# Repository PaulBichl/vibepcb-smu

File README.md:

# VibePCB SMU

A 1-channel, 4-quadrant source/measure unit (bipolar lab supply that also sinks):
**+-30 V, +-1 A**, powered from a **USB-C PD charger (20 V)**, controlled over **Ethernet**,
voltage and current on two 4-digit 7-segment displays. Designed with
[VibePCB](https://github.com/PaulBichl/vibepcb) (tscircuit -> KiCad).

| Board | Layers | Size | Content |
|-------|--------|------|---------|
| `boards/smu-main` | 4 (top+GND / GND / route+GND / bottom+GND) | 160 x 100 mm | USB-C PD input, rail converters, OPA548 output stage, control loop, 24-bit measurement, STM32G431 + W5500 |
| `boards/smu-front` | 2 (both GND-poured) | 150 x 45 mm | 2x SR420561N displays, TM1640 driver, 6 status LEDs, OUTPUT / MODE buttons |

The boards are joined by a 10-way ribbon (main J5 <-> front J1). The output terminal (main J3:
HI, S+, S-, LO) is wired to front-panel binding posts; the OPA548 (TO-220-7) bolts to a heatsink
on the rear panel (with a fan on J4).

## Look at it

| | Main board | Display board |
|---|---|---|
| Schematic | [PDF](boards/smu-main/hardware/smu-main-schematic.pdf) | [PDF](boards/smu-front/hardware/smu-front-schematic.pdf) |
| Layout | [PDF, one page per copper layer](boards/smu-main/hardware/smu-main-layout.pdf), [front](boards/smu-main/hardware/smu-main-layout-front.png), [back](boards/smu-main/hardware/smu-main-layout-back.png) | [PDF](boards/smu-front/hardware/smu-front-layout.pdf), [front](boards/smu-front/hardware/smu-front-layout-front.png), [back](boards/smu-front/hardware/smu-front-layout-back.png) |
| 3D | [top](boards/smu-main/hardware/smu-main-top.png), [bottom](boards/smu-main/hardware/smu-main-bottom.png) | [top](boards/smu-front/hardware/smu-front-top.png), [bottom](boards/smu-front/hardware/smu-front-bottom.png) |
| BOM (LCSC / MPN) | [CSV](boards/smu-main/hardware/smu-main-bom.csv) | [CSV](boards/smu-front/hardware/smu-front-bom.csv) |
| KiCad project | [kicad/](boards/smu-main/hardware/kicad) | [kicad/](boards/smu-front/hardware/kicad) |

Both boards pass KiCad's DRC and ERC with 0 errors. The KiCad projects open as they are (3D
models left out: they are tens of MB; `pcb fix` downloads them). Gerbers / pick-and-place are
not in the repo: open the project in KiCad and plot them, or build the boards (below) and run
`hatch run pcb fab <board>` for Gerbers, drill, BOM, CPL and a JLCPCB upload set.

## Setup / build

Same as the [CO2 example](https://github.com/PaulBichl/vibepcb-example-co2-monitor): clone
`vibepcb` next to this repo as `VibePCB`, then

```bash
hatch run setup
hatch run pcb all smu-main
hatch run pcb all smu-front
cd boards/smu-main/sim && ./run_cases.sh && ./verify.sh   # loop simulations (ngspice)
```

## Architecture

```
USB-C PD (STUSB4500, 20 V) -> P-FET -> VIN -+-> 5 V buck -> 3.3 V (digital), 3.3 V (analog), -4.35 V (charge pump)
                                            +-> SEPIC (LM5156)            V+ = +4.5 .. +34 V  (PWM-tracked)
                                            +-> inverting (LMR51635)      V- = -5 .. -34 V    (PWM-tracked)
DAC8563 (VSET, ISET) -> summing node -> OPA548 -> relay -> HI ... DUT ... LO -> 0.1 R shunt -> GND
                          ^  ^  current-limit integrators (OPA2192) <- INA828 (-1 V/A)
                          |  +-- S+ (remote sense, 100 R to HI inside)
ADS131M02: V = (S+ - S-)/31, I = INA828 output    STM32G431 <-> W5500 <-> RJ45, TM1640 front panel
```

### Output stage

- OPA548 as inverting summing amplifier with remote sense:
  `V(S+) - V(S-) = 30 V - 24 * VSET` (VSET = DAC A, 0..2.5 V, 16 bit -> ~0.9 mV steps).
  The + input sees S- through the matching divider (120k / 3x 10k), so the shunt drop and the
  LO lead resistance are cancelled. S+/S- fall back to HI/LO through 100 R when no sense leads
  are connected (and to the amplifier output through 4.7k while the relay is open).
- Current limit +-ISET/2 A (ISET = DAC B): two integrators compare the INA828 output (-1 V/A)
  with +-ISET and pull the summing node through diodes. PI zero (12k * 47n) sits on the power
  stage pole (120k * 4.7n). Simulated: stable from a dead short to open circuit, with 10-100 uF
  loads, all four quadrants (`sim/`).
- Fast protection: the OPA548's own current limit, fixed at ~1.1 A by R109 (49.9k ILIM to V-,
  I = 15000 * 4.75 V / (13.75k + R)). It catches load steps in microseconds; the precise analog
  limit takes over within ~2-7 ms.
- Output relay (HFD4/5, both poles in parallel), output TVS (SMBJ36CA), clamp diodes from the
  amplifier output to both rails, 1 uF across the terminals. R118 (0.47 Ohm) between amplifier and
  relay keeps the OPA548 stable into capacitive loads (see Performance estimates).

### Tracking rails

The OPA548 only gets the headroom it needs, which keeps its dissipation low and the supply
span within its 60 V rating:

- Firmware: `V+ = max(Vout_max + 4 V, 4.5 V)`, `V- = min(Vout_min - 4 V, -5 V)` where
  Vout_max/min cover the setpoint and the measured output. Sourcing 1 A at 0 V dissipates ~4.5 W
  instead of ~34 W with fixed rails. Sinking is limited by physics (P = Vout * I goes into the
  heatsink): plan for a firmware power limit (e.g. 25 W, more with the fan).
- Hardware span clamp: a 51 V zener + 1k from V+ into the V- feedback node reduces |V-| when
  V+ - V- would exceed ~52 V, whatever the firmware does.
- At reset (MCU pins high-Z): both rails at minimum (pull-up / pull-down on the PWM pins),
  OPA548 hardware current limit 0 A, OPA548 disabled (opto LED on), relay open.

### Measurement

ADS131M02 (24 bit, simultaneous sampling, internal 1.2 V reference, 8.192 MHz oscillator):
- CH0: `(S+ - S-) / 31` through 0.1 % 300k/10k dividers -> +-36 V full scale.
- CH1: INA828 output, -1 V/A -> +-1.2 A full scale.

Firmware calibrates offset/gain of VSET, ISET and both ADC channels against a DMM (store in
flash) and can close a slow digital loop on top of the analog one.

## Performance estimates (simulated)

`boards/smu-main/sim/perf.sh` runs the loop with TI's vendor models (OPA548, INA828, OPA2192;
`fetch_models.sh` downloads them, they are not committed) in ngspice, rails tracking as the
firmware sets them. DAC8563 noise from its datasheet (90 nV/rtHz DAC + 250 nV/rtHz internal
reference, which also feeds REFN, so it cancels at 0 V out). Not simulated: switcher ripple /
PSRR, drift, INL, layout parasitics.

| Quantity | Estimate |
|----------|----------|
| Setting resolution | V: 0.92 mV (16 bit over 60 V), I limit: 19 uA (16 bit over 1.25 A) |
| Uncalibrated error (nominal parts) | V: +90 mV offset (OPA548 Vos/Ib x noise gain 37); I: +0.7 % gain (INA828 G = 9.93) - both removed by the 2-point calibration; 0.1 % resistors add ~0.15 % gain |
| Measurement noise (ADS131M02, 1 kSPS) | V: ~0.1 mVrms (3 uVrms x 31 divider); I: ~4 uArms (ADC + INA828) |
| Four quadrants | +-10 V / +-1 A source and +-11.5 V / 0.5 A sink cases regulate as set |
| Setpoint bandwidth | 270 Hz (-3 dB); 10-90 % rise 1.24 ms; within 10 mV of a 10 V step after ~4 ms; no overshoot with 1 / 10 / 100 uF loads |
| CV loop | phase margin 53 deg (1 uF on board only), 79 deg (+10 uF), 81 deg (+100 uF); crossover ~450 kHz |
| Output impedance (CV) | 23 mOhm at 10 Hz, 0.2 Ohm at 100 Hz, 0.59 Ohm at 1-10 kHz |
| Load step 0.5 -> 1 A at 10 V | dips 0.29 V, back within 10 mV after 0.63 ms |
| Short at 1 A limit | peak 1.20 A (OPA548 limit), within 1 % of 1 A after 6.6 ms; short removed: no overshoot |
| Output noise (10 Hz-100 kHz) | 97 uVrms at 0 V, 115 uVrms at 30 V; 1.15 uV/rtHz at 1 kHz |
| OPA548 dissipation at 1 A | source: 4-4.5 W (tracking rails); sink: (Vout + 5 V) x I, 35 W at +30 V |
| Heatsink (Tj <= 125 C, Ta 35 C) | 4.5 W: <= 18 K/W (passive); 25 W firmware limit: <= 1.7 K/W (fan); sink at 30 V / 0.71 A max under 25 W |
| USB-C PD input | worst case (source 30 V / 1 A) ~43 W -> ~2.2 A at 20 V: a 60 W (3 A) PD supply |

Found by the vendor models: the OPA548 oscillates into the 1 uF output capacitor (0.73 Vpp at
10 V out, `dc0_without_r118`); the behavioural model (`loop.cir`, single pole) hid it. R118
(0.47 Ohm, 2 W) between the amplifier and the relay isolates it; C104 keeps the fast feedback
on the amplifier side, the remote sense removes its DC drop.

## MCU pin map (STM32G431RBT6, LQFP-64)

No radio: control is over Ethernet only. Flashing: USB DFU over the USB-C (hold BOOT0 = SW2,
press RESET = SW1) or SWD on J6 (3V3, SWDIO, SWCLK, NRST, GND). 8 MHz crystal (Y2) on PF0/PF1.

| Pin | Function | Pin | Function |
|-----|----------|-----|----------|
| PA0 | VIN monitor (VIN/11), ADC1_IN1 | PB0 | PWM V+ (TIM3_CH3, high = minimum) |
| PA1 | V+ monitor (V+/16), ADC1_IN2 | PB1 | PWM V- (TIM3_CH4, low = minimum) |
| PA2 | V- monitor ((3.3*120k + V-*10k)/130k), ADC1_IN3 | PB10 | fan PWM (TIM2_CH3) |
| PA3 | NTC at the OPA548, ADC1_IN4 | PB7 / PA15 | I2C1 SDA / SCL (STUSB4500) |
| PC13 | STUSB4500 ALERT | PC9 | output relay |
| PC8 | OUT_EN: drive low to enable the OPA548 | PA7 / PA5 / PA6 | SPI1 MOSI / SCK / MISO (ADC + DAC) |
| PA4 / PC4 | ADC CS / DAC CS | PA11 / PA12 | USB D- / D+ (DFU + CDC over USB-C) |
| PC5 / PB2 | ADC DRDY / SYNC-RESET | PB12 / PC6 / PC7 | W5500 CS / INT / RST |
| PB15 / PB13 / PB14 | SPI2 MOSI / SCK / MISO (W5500) | PC0 / PC1 | buttons OUTPUT / MODE |
| PC2 / PC3 | display DIN / CLK (TM1640) | | |

Pins are assigned by side: each signal leaves the package on the side facing its destination
(fewer crossings under the chip, easier fan-out). The OPA548 current limit is fixed (R109).

## Firmware notes (not part of this repo yet)

- STUSB4500: program the NVM once to request 20 V (PDO3) so it negotiates without the MCU.
  Without PD (5 V USB from a PC) the logic runs (flashing, Ethernet) but the rails stay off
  (converter UVLO ~13 V).
- DAC8563: enable the internal reference after power-up.
- Output on: rails -> E/S enable -> setpoint ramp from 0 V -> relay. Output off in
  reverse; never switch the relay with current flowing.
- Watchdog: if the firmware stalls, the pins keep their last state; use the STM32 independent watchdog (IWDG)
  to reset (which returns everything to the safe defaults above).
- Remote interface: SCPI over raw TCP (port 5025) is the natural choice.

## Known limits / ideas for v2

- The output is ground-referenced (LO = GND = USB-C GND). With an earthed charger, LO is earthed.
- Single current range (1 A, ~1 uA ADC resolution but INA828 offset ~ +-0.15 mA): a second
  range (10 mA, 10 R shunt) would make it a real low-current SMU.
- Sink power is burned in the OPA548; a regenerative output stage would be the next step.
- Loop compensation and the converter compensation values come from simulation / datasheet
  rules of thumb: verify on the bench (step response, capacitive loads).

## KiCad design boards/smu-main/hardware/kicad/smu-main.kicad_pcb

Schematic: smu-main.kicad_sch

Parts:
C1, C2, C3, C14, C18, C20, C31, C43, C81, C92, C94, C116: 1uF; capacitor_cap0603; LCSC C15849
C4, C11, C17, C36, C51, C52, C53, C54, C55, C63, C64, C65, C66, C67, C68, C70, C80, C82, C83, C84, C87, C88, C89, C90, C91, C93, C96, C107, C113, C114, C115, C117, C120, C121: 100nF; capacitor_cap0603; LCSC C14663
C5: 4.7nF; capacitor_cap0603; LCSC C53987
C6, C28, C42: 100uF; NXA63V100M8_15_LO; MPN NXA63V100M8*15 LO; LCSC C3002361
C7, C8, C9, C29, C30, C37, C38: 2.2uF; capacitor_cap1206; LCSC C170101
C10, C39, C101, C103: 100nF; capacitor_cap0805; LCSC C28233
C12, C13: 22uF; capacitor_cap0805; LCSC C45783
C15, C16, C19, C35, C50, C62, C69: 10uF; capacitor_cap0805; LCSC C15850
C21, C22, C23, C71: 4.7uF; capacitor_cap0603; LCSC C19666
C24, C25, C26, C27, C40, C41, C100, C102: 4.7uF; capacitor_cap1210; LCSC C337978
C32, C85, C86: 47nF; capacitor_cap0603; LCSC C107093
C33, C73: 22nF; capacitor_cap0603; LCSC C21122
C34: 470pF; capacitor_cap0603; LCSC C1620
C60, C61: 15pF; capacitor_cap0603; LCSC C1644
C72, C76, C99: 10nF; capacitor_cap0603; LCSC C57112
C74, C75: 6.8nF; capacitor_cap0603; LCSC C1631
C95: 220nF; capacitor_cap0603; LCSC C21120
C97, C98, C105: 1nF; capacitor_cap0603; LCSC C1588
C104: 4.7nF; capacitor_cap0805; LCSC C107104
C108: 1uF; capacitor_cap1206; LCSC C13832
C111, C112: 22pF; capacitor_cap0603; LCSC C1653
D1: SMBJ24A; MPN SMBJ24A; LCSC C123819
D2, D40, D41: SS5100; MPN SS5100; LCSC C5128814
D3: BZX84C51; MPN BZX84C51; LCSC C213380
D10, D11, D12, D13, D42, D44: 1N4148W; MPN 1N4148W; LCSC C81598
D43: SMBJ36CA; MPN SMBJ36CA; LCSC C114002
FB1, FB2: 1µH; BLM18PG221SN1D; MPN BLM18PG221SN1D; LCSC C80165
J1: TYPE-C 16PIN 2MD(073); TYPE-C_16PIN_2MD_073; MPN TYPE-C 16PIN 2MD(073); LCSC C2765186
J2: HR911105A; MPN HR911105A; LCSC C12074
J3: DG301-5.0-04P-14-1000A(H); DG301-5_0-04P-14-1000A_H; MPN DG301-5.0-04P-14-1000A(H); LCSC C3037697
J4: B2B-XH-A-GU; MPN B2B-XH-A-GU; LCSC C265283
J5: A2541WV-2x5P; MPN A2541WV-2x5P; LCSC C225520
J6: PZ254V-11-05P; MPN PZ254V-11-05P; LCSC C492404
K1: HFD4/5; HFD4_5; MPN HFD4/5; LCSC C23510
L1: 10µH; SWPA6045S100MT; MPN SWPA6045S100MT; LCSC C79272
L2, L3, L4: 22µH; SRP1265A-220M; MPN SRP1265A-220M; LCSC C2041465
Q1: AO4407A; MPN AO4407A; LCSC C2841482
Q2: BSC160N10NS3G; MPN BSC160N10NS3G; LCSC C148261
Q3: MMBT5401(RANGE:200-300); MMBT5401_RANGE_200-300; MPN MMBT5401(RANGE:200-300); LCSC C8326
Q43, Q44: AO3400A; MPN AO3400A; LCSC C20917
R1, R17, R24, R97: 1kΩ; resistor_res0603; LCSC C21190
R2, R7, R18: 1MΩ; resistor_res0603; LCSC C22935
R3, R4, R5, R14, R19, R20, R55, R62, R64, R65: 100kΩ; resistor_res0603; LCSC C25803
R6, R81, R85: 20kΩ; resistor_res0603; LCSC C4184
R8: 390kΩ; resistor_res0603; LCSC C23150
R9: 15mΩ; resistor_res2512; LCSC C154674
R10, R13, R16, R23, R50, R51, R54, R56, R58, R60, R61, R78, R80, R83, R84, R87, R90, R91, R113, R120, R121: 10kΩ; resistor_res0603; LCSC C25804
R11, R109: 49.9kΩ; resistor_res0603; LCSC C23184
R12: 75kΩ; resistor_res0603; LCSC C23242
R15: 4.3kΩ; resistor_res0603; LCSC C23159
R21: 2.4kΩ; resistor_res0603; LCSC C22940
R22: 9.1kΩ; resistor_res0603; LCSC C23260
R52, R53, R114: 4.7kΩ; resistor_res0603; LCSC C23162
R57: 150kΩ; resistor_res0603; LCSC C22807
R59: 120kΩ; resistor_res0603; LCSC C25808
R70: 12.4kΩ; resistor_res0603; LCSC C2930060
R71, R72, R74, R75: 49.9Ω; resistor_res0603; LCSC C23185
R73: 10Ω; resistor_res0603; LCSC C22859
R76, R77: 330Ω; resistor_res0603; LCSC C23138
R82, R86: 12kΩ; resistor_res0603; LCSC C22790
R88, R89, R94, R96, R100, R101, R102, R105, R106, R107: 10kΩ; resistor_res0603; LCSC C95204
R92: 5.6kΩ; resistor_res0603; LCSC C179095
R93, R95: 300kΩ; resistor_res0603; LCSC C335091
R103, R104: 120kΩ; resistor_res0603; LCSC C351687
R108: 680Ω; resistor_res0603; LCSC C23228
R115, R116: 100Ω; resistor_res0603; LCSC C22775
R117: 100mΩ; resistor_res2512; LCSC C500724
R118: 470mΩ; HoJLR2512-2W-470mR-1_-75ppm; MPN HoJLR2512-2W-470mR-1%-75ppm; LCSC C2924582
RT1: 10kΩ; NCP18XH103F03RB; MPN NCP18XH103F03RB; LCSC C13564
SW1, SW2: TS-1187A-B-A-B; MPN TS-1187A-B-A-B; LCSC C318884
U1: STUSB4500QTR; MPN STUSB4500QTR; LCSC C2678061
U2: USBLC6-2SC6; MPN USBLC6-2SC6; LCSC C2687116
U3, U8: LMR51635YDDCR; MPN LMR51635YDDCR; LCSC C45262770
U4: AP2112K-3.3TRG1; AP2112K-3_3TRG1; MPN AP2112K-3.3TRG1; LCSC C51118
U5: ME6211C33M5G-N; MPN ME6211C33M5G-N; LCSC C82942
U6: LM27761DSGR; MPN LM27761DSGR; LCSC C129351
U7: LM5156HPWPR; MPN LM5156HPWPR; LCSC C2867852
U20: STM32G431RBT6; MPN STM32G431RBT6; LCSC C431633
U21: W5500; MPN W5500; LCSC C32843
U30: DAC8563SDGSR; MPN DAC8563SDGSR; LCSC C1554729
U31, U32: OPA2192IDR; MPN OPA2192IDR; LCSC C110074
U33: INA828IDR; MPN INA828IDR; LCSC C544342
U34: ADS131M02IPWR; MPN ADS131M02IPWR; LCSC C2922448
U40: OPA548T; MPN OPA548T; LCSC C138712
U41: PC817C; MPN PC817C; LCSC C22447129
X1: OT2JI-111-8.192M; OT2JI-111-8_192M; MPN OT2JI-111-8.192M; LCSC C7425393
Y1: NX3225SA-25MHz-STD-CSR-6; MPN NX3225SA-25MHz-STD-CSR-6; LCSC C448646
Y2: X50328MSB2GI; MPN X50328MSB2GI; LCSC C115962

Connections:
ADC_CS: U20.18 (PA4), U34.12 (CS#)
ADC_DRDY: U20.23 (PC5), U34.13 (DRDY#)
ADC_RST: U20.26 (PB2), U34.11 (SYNC#/RESET#)
AIN0N: C98.1, R95.2, R96.1, U34.4 (AIN0N)
AIN0P: C97.1, R93.2, R94.1, U34.3 (AIN0P)
AIN1P: C99.1, R97.2, U34.6 (AIN1P)
AMP_ISO: K1.3, K1.6, R118.2
AMP_OUT: C104.1, D40.2 (anode), D41.1 (cathode), R114.1, R118.1, U40.6 (VO)
A_MISO: U20.20 (PA6), U34.15 (DOUT)
A_MOSI: U20.21 (PA7), U30.8 (DIN), U34.16 (DIN)
A_SCK: U20.19 (PA5), U30.7 (SCLK), U34.14 (SCLK)
BOOT0: R51.2, SW2.1 (AB), U20.61 (PB8)
BTN_MODE: C121.1, J5.8, R121.2, U20.9 (PC1)
BTN_OUT: C120.1, J5.7, R120.2, U20.8 (PC0)
CC1: J1.18 (CC1), U1.1 (CC1DB), U1.2 (CC1)
CC2: J1.24 (CC2), U1.4 (CC2), U1.5 (CC2DB)
COMP_P: C34.1, R10.1, U7.8 (COMP)
CPOUT: C22.2, U6.3 (CPOUT)
CS_P: Q2.1 (S), Q2.2 (S), Q2.3 (S), R9.1, U7.7 (CS)
D3_A: D3.1 (A), R24.1
DAC_CS: U20.22 (PC4), U30.6 (SYNC#)
DISP_CLK: J5.6, U20.11 (PC3)
DISP_DIN: J5.5, U20.10 (PC2)
EN_N: R18.2, R19.1, U8.2 (EN)
ES: C105.1, U40.7 (ES), U41.4
ETH_CS: U20.34 (PB12), U21.32 (~SCS)
ETH_INT: R78.2, U20.38 (PC6), U21.36 (~INT)
ETH_RCT: C76.1, J2.5 (RCT), R74.2, R75.2
ETH_RDN: C75.2, J2.6 (RD_NEG), R75.1
ETH_RDP: C74.2, J2.3 (RD_POS), R74.1
ETH_RST: U20.39 (PC7), U21.37 (~RST)
ETH_RXN: C75.1, U21.5 (RXN)
ETH_RXP: C74.1, U21.6 (RXP)
ETH_TCT: C73.1, J2.4 (TCT), R73.2
ETH_TXN: J2.2 (TD_NEG), R72.2, U21.1 (TXN)
ETH_TXP: J2.1 (TD_POS), R71.2, U21.2 (TXP)
E_MISO: U20.36 (PB14), U21.34 (MISO)
E_MOSI: U20.37 (PB15), U21.35 (MOSI)
E_SCK: U20.35 (PB13), U21.33 (SCLK)
FAN_D: D44.2 (anode), J4.2, Q44.3 (D)
FAN_PWM: Q44.1 (G), R64.1, U20.30 (PB10)
FB5: R5.2, R6.1, U3.1 (FB)
FB_N: Q3.3 (C), R20.2, R21.1, R24.2, U8.1 (FB)
FB_P: R14.2, R15.1, R16.2, U7.10 (FB)
GND: C1.2, C2.2, C3.2, C4.2, C5.2, C6.2, C7.2, C8.2, C9.2, C10.2, C12.2, C13.2, C14.2, C15.2, C16.2, C17.2, C18.2, C19.2, C21.2, C22.1, C23.1, C26.2, C27.2, C28.2, C29.2, C30.2, C31.2, C32.2, C33.2, C34.2, C35.2, C40.1, C41.1, C42.1, C43.2, C50.2, C51.2, C52.2, C53.2, C54.2, C55.2, C60.2, C61.2, C62.2, C63.2, C64.2, C65.2, C66.2, C67.2, C68.2, C69.2, C70.2, C71.2, C72.2, C73.2, C76.2, C80.2, C81.2, C82.2, C83.2, C84.1, C87.2, C88.1, C89.2, C90.1, C91.2, C92.2, C93.2, C94.2, C95.2, C96.2, C97.2, C98.2, C99.2, C100.2, C101.2, C102.1, C103.1, C107.2, C111.2, C112.2, C113.2, C114.2, C115.2, C116.2, C117.2, C120.2, C121.2, D1.2 (A), J1.15 (GND1), J1.26 (GND2), J2.8 (CHS_GND), J2.13 (SH1), J2.14 (SH2), J5.3, J5.4, J5.10, J6.5, L3.2, L4.2, Q43.2 (S), Q44.2 (S), R2.2, R6.2, R8.2, R9.2, R11.2, R13.2, R15.2, R20.1, R51.1, R56.2, R58.2, R62.2, R64.2, R65.2, R70.2, R94.2, R96.2, R105.2, R106.2, R107.2, R117.2, RT1.2, SW1.2 (CD), U1.6 (RESET), U1.10 (GND), U1.12 (ADDR0), U1.13 (ADDR1), U1.22 (VSYS), U1.25 (GND), U2.2 (GND), U3.4 (GND), U4.2 (GND), U5.2 (V_{SS}), U6.2 (GND), U6.9 (PAD), U7.5 (PGND), U7.6 (AGND), U7.9 (DITHOFF), U7.15 (AGND), U20.15 (VSS), U20.27 (VSSA), U20.31 (VSS), U20.47 (VSS), U20.63 (VSS), U21.3 (AGND), U21.9 (AGND), U21.14 (AGND), U21.16 (AGND), U21.19 (AGND), U21.23 (RSVD), U21.29 (GND), U21.38 (RSVD), U21.39 (RSVD), U21.40 (RSVD), U21.41 (RSVD), U21.42 (RSVD), U21.48 (AGND), U30.3 (GND), U30.4 (LDAC#), U31.3 (VINA+), U31.5 (VINB+), U32.3 (VINA+), U32.5 (VINB+), U33.3 (+IN), U33.5 (REF), U34.2 (AGND), U34.5 (AIN1N), U34.19 (DGND), U41.2, X1.2 (GND), Y1.2 (GND), Y1.4 (GND)
HI: C108.1, D43.1, J3.1, K1.4, K1.5, R115.1
I2C_SCL: R52.2, U1.7 (SCL), U20.51 (PA15)
I2C_SDA: R53.2, U1.8 (SDA), U20.60 (PB7)
ILIM: R109.1, U40.3 (ILIM)
ISET: R81.1, R90.1, U30.2 (VOUTB)
ISETN: R85.1, R91.2, U32.7 (VOUTB)
ISETN_IN: R90.2, R91.1, U32.6 (VINB-)
J2_LEDG_K: J2.10 (LEDG_K), R76.2
J2_LEDY_K: J2.11 (LEDY_K), R77.2
LIMN_IN: C86.1, D12.1 (cathode), R84.2, R85.2, U31.6 (VINB-)
LIMN_OR: D13.2 (anode), R87.1
LIMN_OUT: D12.2 (anode), D13.1 (cathode), R86.2, U31.7 (VOUTB)
LIMN_Z: C86.2, R86.1
LIMP_IN: C85.1, D10.2 (anode), R80.2, R81.2, U31.2 (VINA-)
LIMP_OR: D11.1 (cathode), R83.1
LIMP_OUT: D10.1 (cathode), D11.2 (anode), R82.2, U31.1 (VOUTA)
LIMP_Z: C85.2, R82.1
LO: C108.2, D43.2, J3.4, R116.1, R117.1, U33.2 (-IN)
NRST: C52.1, J6.4, R50.2, SW1.1 (AB), U20.7 (PG10)
NTC: C107.1, R113.2, RT1.1, U20.17 (PA3)
unnamed: C33.1, R10.2
OSC_8M: U34.17 (CLKIN), X1.3 (OUT)
OSC_IN: C111.1, U20.5 (PF0), Y2.1
OSC_OUT: C112.1, U20.6 (PF1), Y2.2
OUT_EN: R108.2, U20.40 (PC8), U41.1
PD_ALERT: R54.2, U1.19 (ALERT), U20.2 (PC13)
PD_GATE: Q1.4 (G), R3.2, U1.16 (VBUS_EN_SNK)
PWM_VN: R23.1, R62.1, U20.25 (PB1)
PWM_VP: R17.1, R61.2, U20.24 (PB0)
Q3_E: Q3.2 (E), R22.2
REF2V5: C82.1, R88.1, U30.10 (VREFIN/VREFOUT)
REFN: R89.2, R102.1, U32.1 (VOUTA)
REFN_IN: R88.2, R89.1, U32.2 (VINA-)
RELAY: Q43.1 (G), R65.1, U20.41 (PC9)
RLY_D: D42.2 (anode), K1.8, Q43.3 (D)
SEP_MID: C24.2, C25.2, D2.2 (anode), L3.1
SMINUS: J3.3, R95.1, R104.1, R116.2
SPLUS: J3.2, R93.1, R103.1, R114.2, R115.2
SUMN: C104.2, R83.2, R87.2, R100.2, R101.2, R102.2, R103.2, U40.2 (VIN-)
SUMP: R104.2, R105.1, R106.1, R107.1, U40.1 (VIN+)
SW5: C11.2, L1.1, U3.5 (SW)
SWCLK: J6.3, U20.50 (PA14)
SWDIO: J6.2, U20.49 (PA13)
SW_N: C36.2, L4.1, U8.5 (SW)
SW_P: C24.1, C25.1, L2.2, Q2.5 (D), Q2.6 (D), Q2.7 (D), Q2.8 (D), Q2.9 (D)
U1_VBUS_VS_DISCH: R1.2, U1.18 (VBUS_VS_DISCH)
U1_VREG_1V2: C2.1, U1.21 (VREG_1V2)
U1_VREG_2V7: C3.1, U1.23 (VREG_2V7)
U3_CB: C11.1, U3.6 (CB)
U3_EN: R4.2, U3.2 (EN)
U6_C1_NEG: C20.2, U6.7 (C-)
U6_C1_POS: C20.1, U6.8 (C+)
U7_GATE: Q2.4 (G), U7.4 (GATE)
U7_RT: R11.1, U7.12 (RT)
U7_SS: C32.1, U7.11 (SS)
U7_VCC: C31.1, U7.3 (VCC)
U8_CB: C36.1, U8.6 (CB)
U21_1V2O: C72.1, U21.22 (1V2O)
U21_ACTLED: R77.1, U21.27 (ACTLED)
U21_EXRES1: R70.1, U21.10 (EXRES1)
U21_LINKLED: R76.1, U21.25 (LINKLED)
U21_TOCAP: C71.1, U21.20 (TOCAP)
U33_RG1: R92.1, U33.8 (RG)
U33_RG2: R92.2, U33.1 (RG)
U34_CAP: C95.1, U34.18 (CAP)
USB_DN: J1.19 (Dn2), J1.21 (Dn1), U2.1 (I/O1), U2.6 (I/O1), U20.45 (PA11)
USB_DP: J1.20 (Dp1), J1.22 (Dp2), U2.3 (I/O2), U2.4 (I/O2), U20.46 (PA12)
USB_SHIELD: C5.1, J1.13 (EH1), J1.14 (EH2), J1.27 (EH3), J1.28 (EH4), R2.1
UVLO_P: R12.2, R13.1, U7.14 (EN/UVLO/SYNC)
V3V3: C15.1, C50.1, C51.1, C69.1, C70.1, C93.1, C94.1, C96.1, C113.1, C114.1, C115.1, C116.1, C117.1, FB2.1, J2.9 (LEDG_A), J2.12 (LEDY_A), J5.9, J6.1, R22.1, R50.1, R52.1, R53.1, R54.1, R60.1, R61.1, R78.1, R108.1, R113.1, R120.1, R121.1, SW2.2 (CD), U2.5 (VBUS), U4.5 (VOUT), U20.1 (VBAT), U20.16 (VDD), U20.28 (VREF+), U20.29 (VDDA), U20.32 (VDD), U20.48 (VDD), U20.64 (VDD), U21.28 (VDD), U34.20 (DVDD), X1.1 (Tri-State), X1.4 (VDD)
V3V3A: C18.1, C19.1, C80.1, C81.1, C91.1, C92.1, U5.5 (V_{OUT}), U30.5 (CLR#), U30.9 (AVDD), U34.1 (AVDD)
V3V3_ETH: C62.1, C63.1, C64.1, C65.1, C66.1, C67.1, C68.1, FB2.2, R71.1, R72.1, R73.1, U21.4 (AVDD), U21.8 (AVDD), U21.11 (AVDD), U21.15 (AVDD), U21.17 (AVDD), U21.21 (AVDD)
V5: C12.1, C13.1, C14.1, D42.1 (cathode), D44.1 (cathode), FB1.1, J4.1, J5.1, J5.2, K1.1, L1.2, R5.1, U4.1 (VIN), U4.3 (EN)
V5A: C16.1, C17.1, C21.1, C83.1, C87.1, C89.1, FB1.2, U5.1 (V_{IN}), U5.3 (CE), U6.1 (VIN), U6.6 (EN), U31.8 (VDD), U32.8 (VDD), U33.7 (+VS)
VBUS: C1.1, C4.1, J1.16 (VBUS1), J1.25 (VBUS2), Q1.1 (S), Q1.2 (S), Q1.3 (S), R1.1, R3.1, U1.24 (VDD)
VI: R80.1, R84.1, R97.1, U33.6 (OUT)
VIN: C6.1, C7.1, C8.1, C9.1, C10.1, C29.1, C30.1, C37.1, C38.1, C39.1, D1.1 (C), L2.1, Q1.5 (D), Q1.6 (D), Q1.7 (D), Q1.8 (D), R4.1, R12.1, R18.1, R55.1, U3.3 (VIN), U7.1 (BIAS), U8.3 (VIN)
VIN_MON: C53.1, R55.2, R56.1, U20.12 (PA0)
VN: C37.2, C38.2, C39.2, C40.2, C41.2, C42.2, C102.2, C103.2, C105.2, D41.2 (anode), R19.2, R21.2, R59.1, R109.2, U8.4 (GND), U40.4 (V-), U41.3
VNA: C23.2, C84.2, C88.2, C90.2, R7.1, U6.4 (VOUT), U31.4 (VSS), U32.4 (VSS), U33.4 (-VS)
VNA_FB: R7.2, R8.1, U6.5 (VFB)
VN_CTL: C43.1, Q3.1 (B), R23.2
VN_MON: C55.1, R59.2, R60.2, U20.14 (PA2)
VP: C26.1, C27.1, C28.1, C100.1, C101.1, D2.1 (cathode), D3.3 (K), D40.1 (cathode), R14.1, R57.1, U40.5 (V+)
VP_CTL: C35.1, R16.1, R17.2
VP_MON: C54.1, R57.2, R58.1, U20.13 (PA1)
VSET: R100.1, R101.1, U30.1 (VOUTA)
XI: C60.1, U21.30 (XI/CLKIN), Y1.1
XO: C61.1, U21.31 (XO), Y1.3

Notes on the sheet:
USB-C PD input
logic supplies
V+ rail: SEPIC
V- rail: inverting buck-boost
MCU
Ethernet
analog control & measurement
output stage
fan, front panel

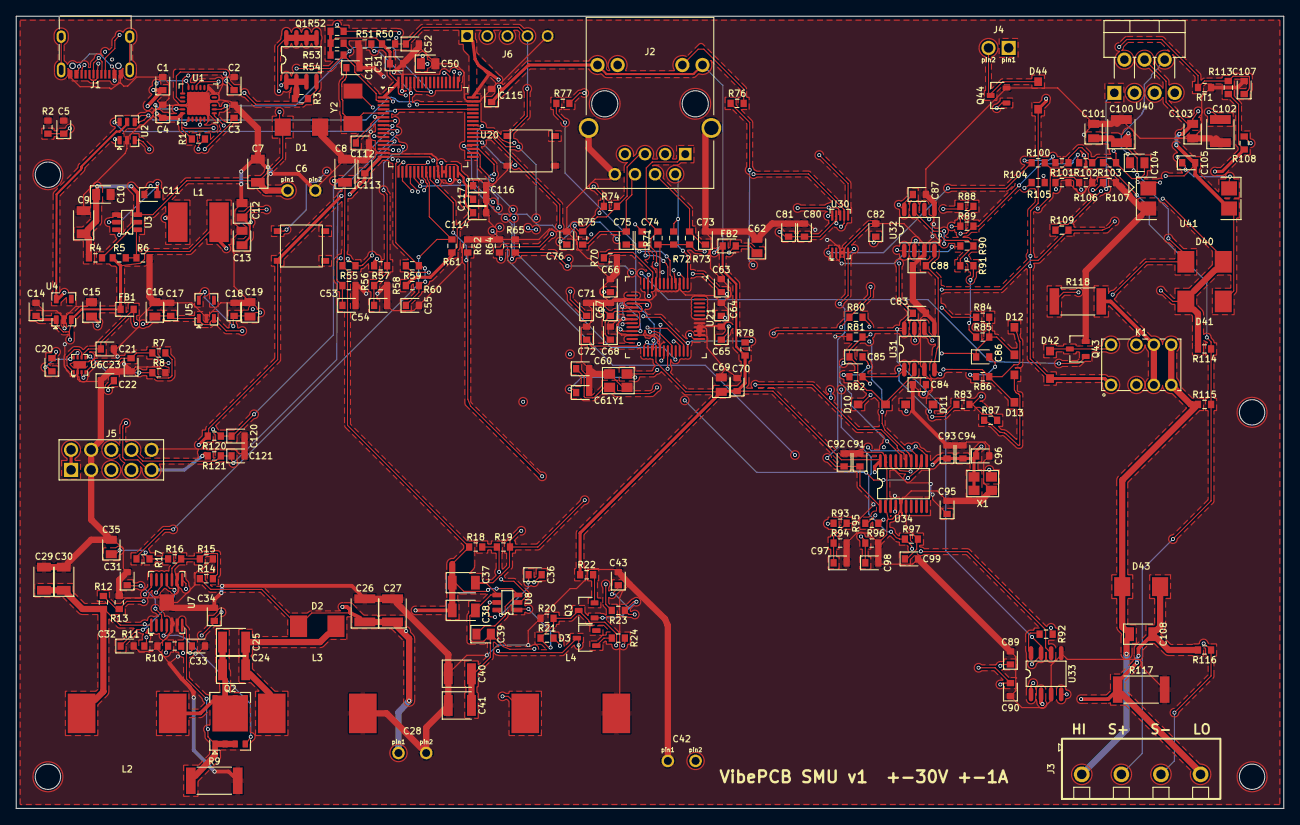
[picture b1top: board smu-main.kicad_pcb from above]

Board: 4 copper layers, 160.0 x 100.0 mm, 240 parts (0 on the bottom side), 134 nets.

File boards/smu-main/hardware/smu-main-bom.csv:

"Qty","Designator","Value","Footprint","MPN","LCSC Part #"
"12","C1,C2,C3,C14,C18,C20,C31,C43,C81,C92,C94,C116","1uF","tscircuit:capacitor_cap0603","","C15849"
"34","C4,C11,C17,C36,C51,C52,C53,C54,C55,C63,C64,C65,C66,C67,C68,C70,C80,C82,C83,C84,C87,C88,C89,C90,C91,C93,C96,C107,C113,C114,C115,C117,C120,C121","100nF","tscircuit:capacitor_cap0603","","C14663"
"1","C5","4.7nF","tscircuit:capacitor_cap0603","","C53987"
"3","C6,C28,C42","100uF","tscircuit:NXA63V100M8_15_LO","NXA63V100M8*15 LO","C3002361"
"7","C7,C8,C9,C29,C30,C37,C38","2.2uF","tscircuit:capacitor_cap1206","","C170101"
"4","C10,C39,C101,C103","100nF","tscircuit:capacitor_cap0805","","C28233"
"2","C12,C13","22uF","tscircuit:capacitor_cap0805","","C45783"
"7","C15,C16,C19,C35,C50,C62,C69","10uF","tscircuit:capacitor_cap0805","","C15850"
"4","C21,C22,C23,C71","4.7uF","tscircuit:capacitor_cap0603","","C19666"
"8","C24,C25,C26,C27,C40,C41,C100,C102","4.7uF","tscircuit:capacitor_cap1210","","C337978"
"3","C32,C85,C86","47nF","tscircuit:capacitor_cap0603","","C107093"
"2","C33,C73","22nF","tscircuit:capacitor_cap0603","","C21122"
"1","C34","470pF","tscircuit:capacitor_cap0603","","C1620"
"2","C60,C61","15pF","tscircuit:capacitor_cap0603","","C1644"
"3","C72,C76,C99","10nF","tscircuit:capacitor_cap0603","","C57112"
"2","C74,C75","6.8nF","tscircuit:capacitor_cap0603","","C1631"
"1","C95","220nF","tscircuit:capacitor_cap0603","","C21120"
"3","C97,C98,C105","1nF","tscircuit:capacitor_cap0603","","C1588"
"1","C104","4.7nF","tscircuit:capacitor_cap0805","","C107104"
"1","C108","1uF","tscircuit:capacitor_cap1206","","C13832"
"2","C111,C112","22pF","tscircuit:capacitor_cap0603","","C1653"
"1","D1","SMBJ24A","tscircuit:SMBJ24A","SMBJ24A","C123819"
"3","D2,D40,D41","SS5100","tscircuit:SS5100","SS5100","C5128814"
"1","D3","BZX84C51","tscircuit:BZX84C51","BZX84C51","C213380"
"6","D10,D11,D12,D13,D42,D44","1N4148W","tscircuit:1N4148W","1N4148W","C81598"
"1","D43","SMBJ36CA","tscircuit:SMBJ36CA","SMBJ36CA","C114002"
"2","FB1,FB2","1µH","tscircuit:BLM18PG221SN1D","BLM18PG221SN1D","C80165"
"1","J1","TYPE-C 16PIN 2MD(073)","tscircuit:TYPE-C_16PIN_2MD_073","TYPE-C 16PIN 2MD(073)","C2765186"
"1","J2","HR911105A","tscircuit:HR911105A","HR911105A","C12074"
"1","J3","DG301-5.0-04P-14-1000A(H)","tscircuit:DG301-5_0-04P-14-1000A_H","DG301-5.0-04P-14-1000A(H)","C3037697"
"1","J4","B2B-XH-A-GU","tscircuit:B2B-XH-A-GU","B2B-XH-A-GU","C265283"
"1","J5","A2541WV-2x5P","tscircuit:A2541WV-2x5P","A2541WV-2x5P","C225520"
"1","J6","PZ254V-11-05P","tscircuit:PZ254V-11-05P","PZ254V-11-05P","C492404"
"1","K1","HFD4/5","tscircuit:HFD4_5","HFD4/5","C23510"
"1","L1","10µH","tscircuit:SWPA6045S100MT","SWPA6045S100MT","C79272"
"3","L2,L3,L4","22µH","tscircuit:SRP1265A-220M","SRP1265A-220M","C2041465"
"1","Q1","AO4407A","tscircuit:AO4407A","AO4407A","C2841482"
"1","Q2","BSC160N10NS3G","tscircuit:BSC160N10NS3G","BSC160N10NS3G","C148261"
"1","Q3","MMBT5401(RANGE:200-300)","tscircuit:MMBT5401_RANGE_200-300","MMBT5401(RANGE:200-300)","C8326"
"2","Q43,Q44","AO3400A","tscircuit:AO3400A","AO3400A","C20917"
"4","R1,R17,R24,R97","1kΩ","tscircuit:resistor_res0603","","C21190"
"3","R2,R7,R18","1MΩ","tscircuit:resistor_res0603","","C22935"
"10","R3,R4,R5,R14,R19,R20,R55,R62,R64,R65","100kΩ","tscircuit:resistor_res0603","","C25803"
"3","R6,R81,R85","20kΩ","tscircuit:resistor_res0603","","C4184"
"1","R8","390kΩ","tscircuit:resistor_res0603","","C23150"
"1","R9","15mΩ","tscircuit:resistor_res2512","","C154674"
"21","R10,R13,R16,R23,R50,R51,R54,R56,R58,R60,R61,R78,R80,R83,R84,R87,R90,R91,R113,R120,R121","10kΩ","tscircuit:resistor_res0603","","C25804"
"2","R11,R109","49.9kΩ","tscircuit:resistor_res0603","","C23184"
"1","R12","75kΩ","tscircuit:resistor_res0603","","C23242"
"1","R15","4.3kΩ","tscircuit:resistor_res0603","","C23159"
"1","R21","2.4kΩ","tscircuit:resistor_res0603","","C22940"
"1","R22","9.1kΩ","tscircuit:resistor_res0603","","C23260"
"3","R52,R53,R114","4.7kΩ","tscircuit:resistor_res0603","","C23162"
"1","R57","150kΩ","tscircuit:resistor_res0603","","C22807"
"1","R59","120kΩ","tscircuit:resistor_res0603","","C25808"
"1","R70","12.4kΩ","tscircuit:resistor_res0603","","C2930060"
"4","R71,R72,R74,R75","49.9Ω","tscircuit:resistor_res0603","","C23185"
"1","R73","10Ω","tscircuit:resistor_res0603","","C22859"
"2","R76,R77","330Ω","tscircuit:resistor_res0603","","C23138"
"2","R82,R86","12kΩ","tscircuit:resistor_res0603","","C22790"
"10","R88,R89,R94,R96,R100,R101,R102,R105,R106,R107","10kΩ","tscircuit:resistor_res0603","","C95204"
"1","R92","5.6kΩ","tscircuit:resistor_res0603","","C179095"
"2","R93,R95","300kΩ","tscircuit:resistor_res0603","","C335091"
"2","R103,R104","120kΩ","tscircuit:resistor_res0603","","C351687"
"1","R108","680Ω","tscircuit:resistor_res0603","","C23228"
"2","R115,R116","100Ω","tscircuit:resistor_res0603","","C22775"
"1","R117","100mΩ","tscircuit:resistor_res2512","","C500724"
"1","R118","470mΩ","tscircuit:HoJLR2512-2W-470mR-1_-75ppm","HoJLR2512-2W-470mR-1%-75ppm","C2924582"
"1","RT1","10kΩ","tscircuit:NCP18XH103F03RB","NCP18XH103F03RB","C13564"
"2","SW1,SW2","TS-1187A-B-A-B","tscircuit:TS-1187A-B-A-B","TS-1187A-B-A-B","C318884"
"1","U1","STUSB4500QTR","tscircuit:STUSB4500QTR","STUSB4500QTR","C2678061"
"1","U2","USBLC6-2SC6","tscircuit:USBLC6-2SC6","USBLC6-2SC6","C2687116"
"2","U3,U8","LMR51635YDDCR","tscircuit:LMR51635YDDCR","LMR51635YDDCR","C45262770"
"1","U4","AP2112K-3.3TRG1","tscircuit:AP2112K-3_3TRG1","AP2112K-3.3TRG1","C51118"
"1","U5","ME6211C33M5G-N","tscircuit:ME6211C33M5G-N","ME6211C33M5G-N","C82942"
"1","U6","LM27761DSGR","tscircuit:LM27761DSGR","LM27761DSGR","C129351"
"1","U7","LM5156HPWPR","tscircuit:LM5156HPWPR","LM5156HPWPR","C2867852"
"1","U20","STM32G431RBT6","tscircuit:STM32G431RBT6","STM32G431RBT6","C431633"
"1","U21","W5500","tscircuit:W5500","W5500","C32843"
"1","U30","DAC8563SDGSR","tscircuit:DAC8563SDGSR","DAC8563SDGSR","C1554729"
"2","U31,U32","OPA2192IDR","tscircuit:OPA2192IDR","OPA2192IDR","C110074"
"1","U33","INA828IDR","tscircuit:INA828IDR","INA828IDR","C544342"
"1","U34","ADS131M02IPWR","tscircuit:ADS131M02IPWR","ADS131M02IPWR","C2922448"
"1","U40","OPA548T","tscircuit:OPA548T","OPA548T","C138712"
"1","U41","PC817C","tscircuit:PC817C","PC817C","C22447129"
"1","X1","OT2JI-111-8.192M","tscircuit:OT2JI-111-8_192M","OT2JI-111-8.192M","C7425393"
"1","Y1","NX3225SA-25MHz-STD-CSR-6","tscircuit:NX3225SA-25MHz-STD-CSR-6","NX3225SA-25MHz-STD-CSR-6","C448646"
"1","Y2","X50328MSB2GI","tscircuit:X50328MSB2GI","X50328MSB2GI","C115962"

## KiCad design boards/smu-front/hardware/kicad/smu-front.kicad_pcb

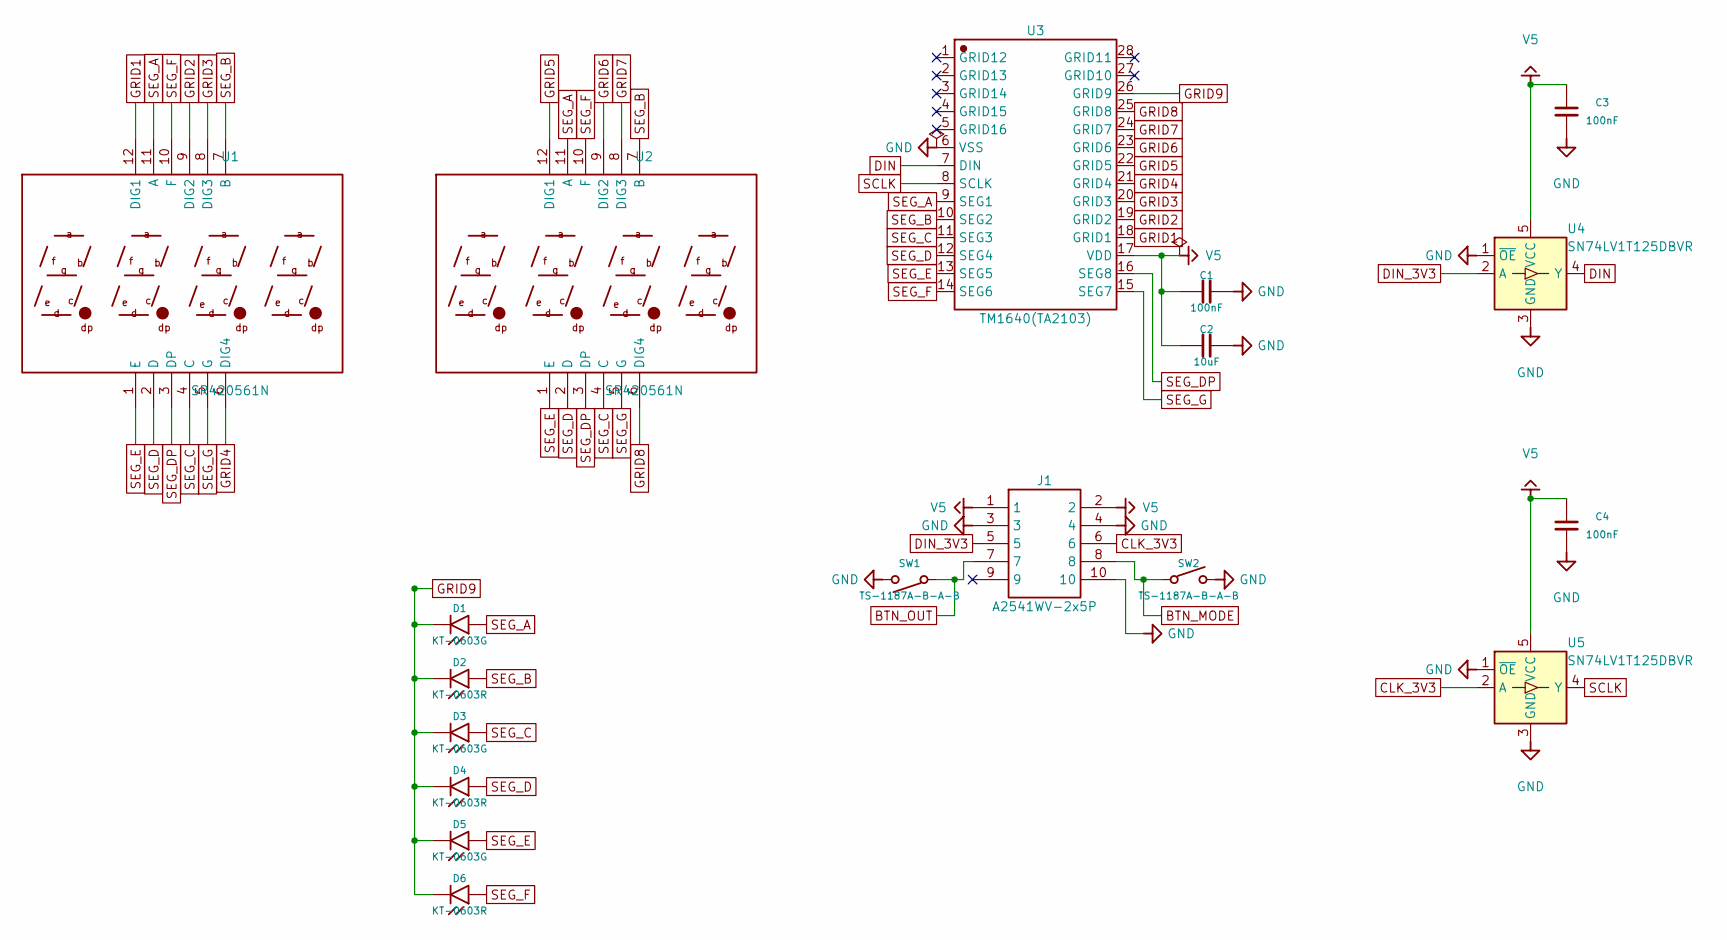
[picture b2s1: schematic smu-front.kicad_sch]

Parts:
C1, C3, C4: 100nF; capacitor_cap0603; LCSC C14663
C2: 10uF; capacitor_cap0805; LCSC C15850
D1, D3, D5: KT-0603G; MPN KT-0603G; LCSC C12624
D2, D4, D6: KT-0603R; MPN KT-0603R; LCSC C2286
J1: A2541WV-2x5P; MPN A2541WV-2x5P; LCSC C225520
SW1, SW2: TS-1187A-B-A-B; MPN TS-1187A-B-A-B; LCSC C318884
U1, U2: SR420561N; MPN SR420561N; LCSC C109200
U3: TM1640(TA2103); TM1640_TA2103; MPN TM1640(TA2103); LCSC C5337152
U4, U5: SN74LV1T125DBVR; MPN SN74LV1T125DBVR; LCSC C473338

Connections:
BTN_MODE: J1.8, SW2.1 (AB)
BTN_OUT: J1.7, SW1.1 (AB)
CLK_3V3: J1.6, U5.2 (A)
DIN: U3.7 (DIN), U4.4 (Y)
DIN_3V3: J1.5, U4.2 (A)
GND: C1.2, C2.2, C3.2, C4.2, J1.3, J1.4, J1.10, SW1.2 (CD), SW2.2 (CD), U3.6 (VSS), U4.1 (~OE), U4.3 (GND), U5.1 (~OE), U5.3 (GND)
GRID1: U1.12 (DIG1), U3.18 (GRID1)
GRID2: U1.9 (DIG2), U3.19 (GRID2)
GRID3: U1.8 (DIG3), U3.20 (GRID3)
GRID4: U1.6 (DIG4), U3.21 (GRID4)
GRID5: U2.12 (DIG1), U3.22 (GRID5)
GRID6: U2.9 (DIG2), U3.23 (GRID6)
GRID7: U2.8 (DIG3), U3.24 (GRID7)
GRID8: U2.6 (DIG4), U3.25 (GRID8)
GRID9: D1.1 (cathode), D2.2 (cathode), D3.1 (cathode), D4.2 (cathode), D5.1 (cathode), D6.2 (cathode), U3.26 (GRID9)
SCLK: U3.8 (SCLK), U5.4 (Y)
SEG_A: D1.2 (anode), U1.11 (A), U2.11 (A), U3.9 (SEG1)
SEG_B: D2.1 (anode), U1.7 (B), U2.7 (B), U3.10 (SEG2)
SEG_C: D3.2 (anode), U1.4 (C), U2.4 (C), U3.11 (SEG3)
SEG_D: D4.1 (anode), U1.2 (D), U2.2 (D), U3.12 (SEG4)
SEG_DP: U1.3 (DP), U2.3 (DP), U3.16 (SEG8)
SEG_E: D5.2 (anode), U1.1 (E), U2.1 (E), U3.13 (SEG5)
SEG_F: D6.1 (anode), U1.10 (F), U2.10 (F), U3.14 (SEG6)
SEG_G: U1.5 (G), U2.5 (G), U3.15 (SEG7)
V5: C1.1, C2.1, C3.1, C4.1, J1.1, J1.2, U3.17 (VDD), U4.5 (VCC), U5.5 (VCC)

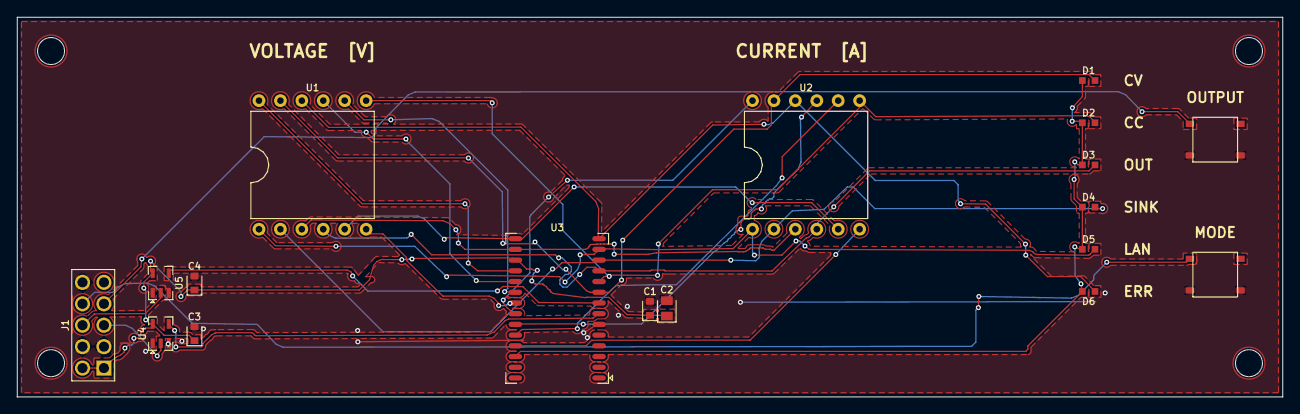
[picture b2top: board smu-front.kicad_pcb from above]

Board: 2 copper layers, 150.0 x 45.0 mm, 18 parts (0 on the bottom side), 25 nets.

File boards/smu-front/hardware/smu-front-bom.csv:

"Qty","Designator","Value","Footprint","MPN","LCSC Part #"
"3","C1,C3,C4","100nF","tscircuit:capacitor_cap0603","","C14663"
"1","C2","10uF","tscircuit:capacitor_cap0805","","C15850"
"3","D1,D3,D5","KT-0603G","tscircuit:KT-0603G","KT-0603G","C12624"
"3","D2,D4,D6","KT-0603R","tscircuit:KT-0603R","KT-0603R","C2286"
"1","J1","A2541WV-2x5P","tscircuit:A2541WV-2x5P","A2541WV-2x5P","C225520"
"2","SW1,SW2","TS-1187A-B-A-B","tscircuit:TS-1187A-B-A-B","TS-1187A-B-A-B","C318884"
"2","U1,U2","SR420561N","tscircuit:SR420561N","SR420561N","C109200"
"1","U3","TM1640(TA2103)","tscircuit:TM1640_TA2103","TM1640(TA2103)","C5337152"
"2","U4,U5","SN74LV1T125DBVR","tscircuit:SN74LV1T125DBVR","SN74LV1T125DBVR","C473338"
